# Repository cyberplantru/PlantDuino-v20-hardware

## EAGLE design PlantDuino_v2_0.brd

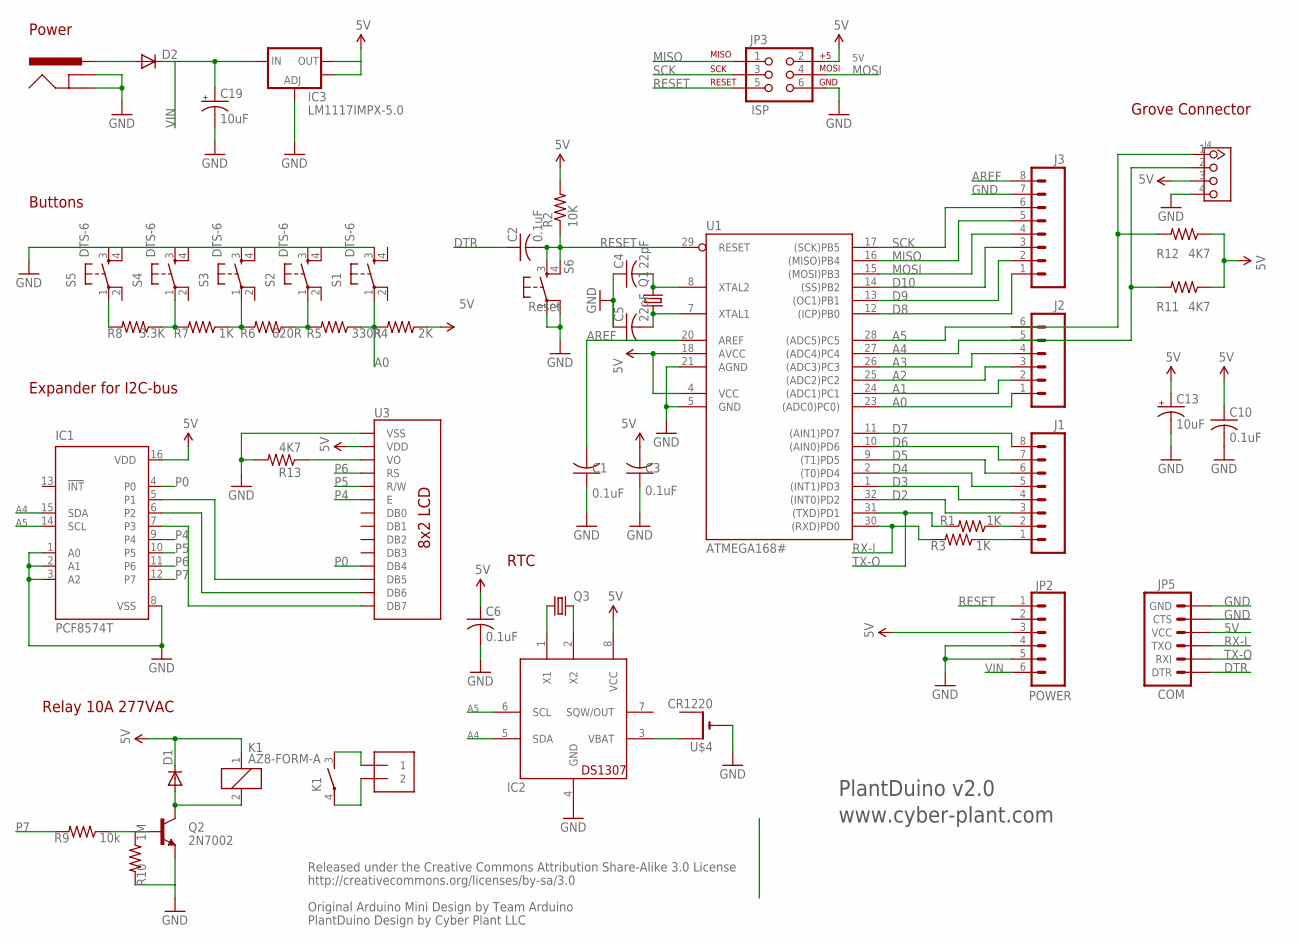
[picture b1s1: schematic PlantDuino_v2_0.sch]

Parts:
C1, C2, C3, C6, C10: 0.1uF; C1206
C4, C5: 22pF; C1206
C13, C19: 10uF; EIA6032
D1, D2: DIODESMA; SMA-DIODE
IC1: PCF8574T; SO16W
IC2: DS1307; SO08
IC3: LM1117IMPX-5.0; SOT223
J1, J3: M08LONGPADS; 1X08_LONGPADS
J2: M06LONGPADS; 1X06_LONGPADS
J4: TWIG-4P-2.090D; 4P-2.0-90D
JP1: 1X2-3.5MM
JP2: POWER; 1X06_LONGPADS
JP3: ISP; 2X3
JP4: Power Jack; POWER_JACK_PTH
JP5: COM; 1X06
K1: AZ8-FORM-A; AZ8
Q1: CRYTALHC49S; HC49/S@1
Q2: 2N7002; SOT23
Q3: CRYSTALTC26H; TC26H
R1, R3, R7: 1K; 1206
R2: 10K; 1206
R4: 2K; 1206
R5: 330R; 1206
R6: 620R; 1206
R8: 3.3K; 1206
R9: 10k; 1206
R10: 1M; 1206
R11, R12, R13: 4K7; 1206
S1, S2, S3, S4, S5: DTS-6
S6: Reset; DTS-6
U1: ATMEGA168#; TQFP32-08
U3: LCD-8X2-WH0802A8X2; LCD-8X2-WH0802A
U$4: CR1220; CR1220-THM

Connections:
5V: C3.2, C6.1, C10.1, C13.P$1 (+), D1.C, IC1.16 (VDD), IC2.8 (VCC), IC3.2 (OUT), IC3.4 (OUT), J4.3, JP2.3, JP3.2, JP5.4 (VCC), K1.1, R2.2, R4.1, R11.1, R12.1, U1.4 (VCC), U1.18 (AVCC), U3.2 (VDD)
A0: J2.1, R4.2, R5.1, S1.1, U1.23 ((ADC0)PC0))
A1: J2.2, U1.24 ((ADC1)PC1)
A2: J2.3, U1.25 ((ADC2)PC2)
A3: J2.4, U1.26 ((ADC3)PC3)
A4: IC1.15 (SDA), IC2.5 (SDA), J2.5, J4.2, R11.2, U1.27 ((ADC4)PC4)
A5: IC1.14 (SCL), IC2.6 (SCL), J2.6, J4.1, R12.2, U1.28 ((ADC5)PC5)
AREF: C1.2, J3.8, U1.20 (AREF)
D2: J1.3, U1.32 ((INT0)PD2)
D3: J1.4, U1.1 ((INT1)PD3)
D4: J1.5, U1.2 ((T0)PD4)
D5: J1.6, U1.9 ((T1)PD5)
D6: J1.7, U1.10 ((AIN0)PD6)
D7: J1.8, U1.11 ((AIN1)PD7)
D8: J3.1, U1.12 ((ICP)PB0)
D9: J3.2, U1.13 ((OC1)PB1)
D10: J3.3, U1.14 ((SS)PB2)
DTR: C2.1, JP5.1 (DTR)
GND: C1.1, C3.1, C4.1, C5.1, C6.2, C10.2, C13.P$2 (-), C19.P$2 (-), IC1.1 (A0), IC1.2 (A1), IC1.3 (A2), IC1.8 (VSS), IC2.4 (GND), IC3.1 (ADJ), J3.7, J4.4, JP2.4, JP2.5, JP3.6, JP4.GND, JP4.GNDBREAK, JP5.5 (CTS), JP5.6 (GND), Q2.2 (E), R10.2, R13.2, S1.3, S2.3, S2.4, S3.3, S3.4, S4.3, S4.4, S5.3, S5.4, S6.1, S6.2, U1.5 (GND), U1.21 (AGND), U3.1 (VSS), U$4.-
MISO: J3.5, JP3.1, U1.16 ((MISO)PB4)
MOSI: J3.4, JP3.4, U1.15 ((MOSI)PB3)
unnamed: R13.1, U3.3 (VO)
unnamed: C4.2, Q1.2, U1.8 (XTAL2)
unnamed: C5.2, Q1.1, U1.7 (XTAL1)
unnamed: D2.A, JP4.PWR
unnamed: IC1.7 (P3), U3.14 (DB7)
unnamed: IC1.6 (P2), U3.13 (DB6)
unnamed: IC1.5 (P1), U3.12 (DB5)
unnamed: IC2.3 (VBAT), U$4.+1 (+)
unnamed: JP1.2, K1.4
unnamed: JP1.1, K1.3 (S)
unnamed: Q2.1 (B), R9.1, R10.1
unnamed: R5.2, R6.1, S2.1
unnamed: R6.2, R7.1, S3.1
unnamed: R7.2, R8.1, S4.1
unnamed: R8.2, S5.1
unnamed: IC2.1 (X1), Q3.1
unnamed: D1.A, K1.2, Q2.3 (C)
unnamed: IC2.2 (X2), Q3.2
P0: IC1.4 (P0), U3.11 (DB4)
P4: IC1.9 (P4), U3.6 (E)
P5: IC1.10 (P5), U3.5 (R/W)
P6: IC1.11 (P6), U3.4 (RS)
P7: IC1.12 (P7), R9.2
RESET: C2.2, JP2.1, JP3.5, R2.1, S6.3, S6.4, U1.29 (RESET)
RX-I: JP5.3 (TXO), R3.2, U1.30 ((RXD)PD0)
RX-IP: J1.2, R1.1
SCK: J3.6, JP3.3, U1.17 ((SCK)PB5)
TX-O: JP5.2 (RXI), R1.2, U1.31 ((TXD)PD1)
TX-OP: J1.1, R3.1
VIN: C19.P$1 (+), D2.C, IC3.3 (IN), JP2.6

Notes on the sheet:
Released under the Creative Commons Attribution Share-Alike 3.0 License
http://creativecommons.org/licenses/by-sa/3.0
Original Arduino Mini Design by Team Arduino
Power
Buttons
PlantDuino Design by Cyber Plant LLC
Grove Connector
Relay 10A 277VAC
Expander for I2C-bus
RTC
PlantDuino v2.0
www.cyber-plant.com

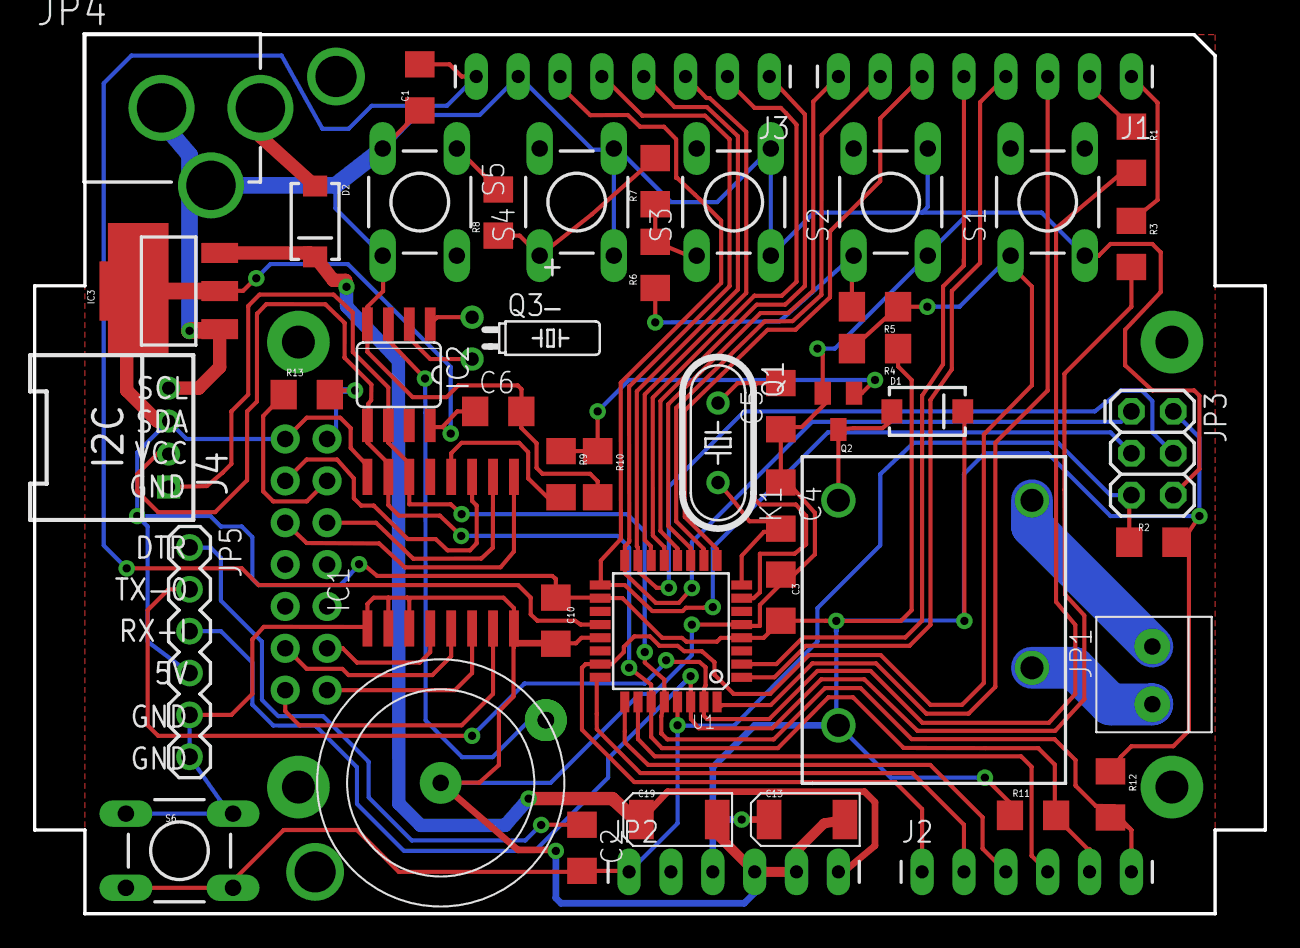
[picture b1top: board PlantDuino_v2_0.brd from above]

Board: 2 copper layers, 74.7 x 53.3 mm, 49 parts (1 on the bottom side), 51 nets.

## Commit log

2014-10-21 master

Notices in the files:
parts and their libraries:
wh0802a3: Licensing: CC v3.0 Share-Alike You are welcome to use this library for commercial purposes.
